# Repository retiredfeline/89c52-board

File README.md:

# 89c52 clock board

These are the design files for the 89C52 clock PCB described in [this Hackaday project](https://hackaday.io/project/175986-89c52-clock-board). It plugs onto the back of the [6 segment](https://hackaday.io/project/175397-6-segment-2-digit-led-display-board) and [7 segment](https://hackaday.io/project/175432-7-segment-2-digit-led-display-board) cascadable boards. The firmware is published at [89C52 clock](https://github.com/kenyapcomau/89c52-clock).

## Versioning

First release December 2020

## Notes

Not all the component locations on the board need to be populated, see the notes in the schematic.

## Authors

* **Ken Yap**

## License

See the [LICENSE](LICENSE.md) file for license rights and limitations (MIT).

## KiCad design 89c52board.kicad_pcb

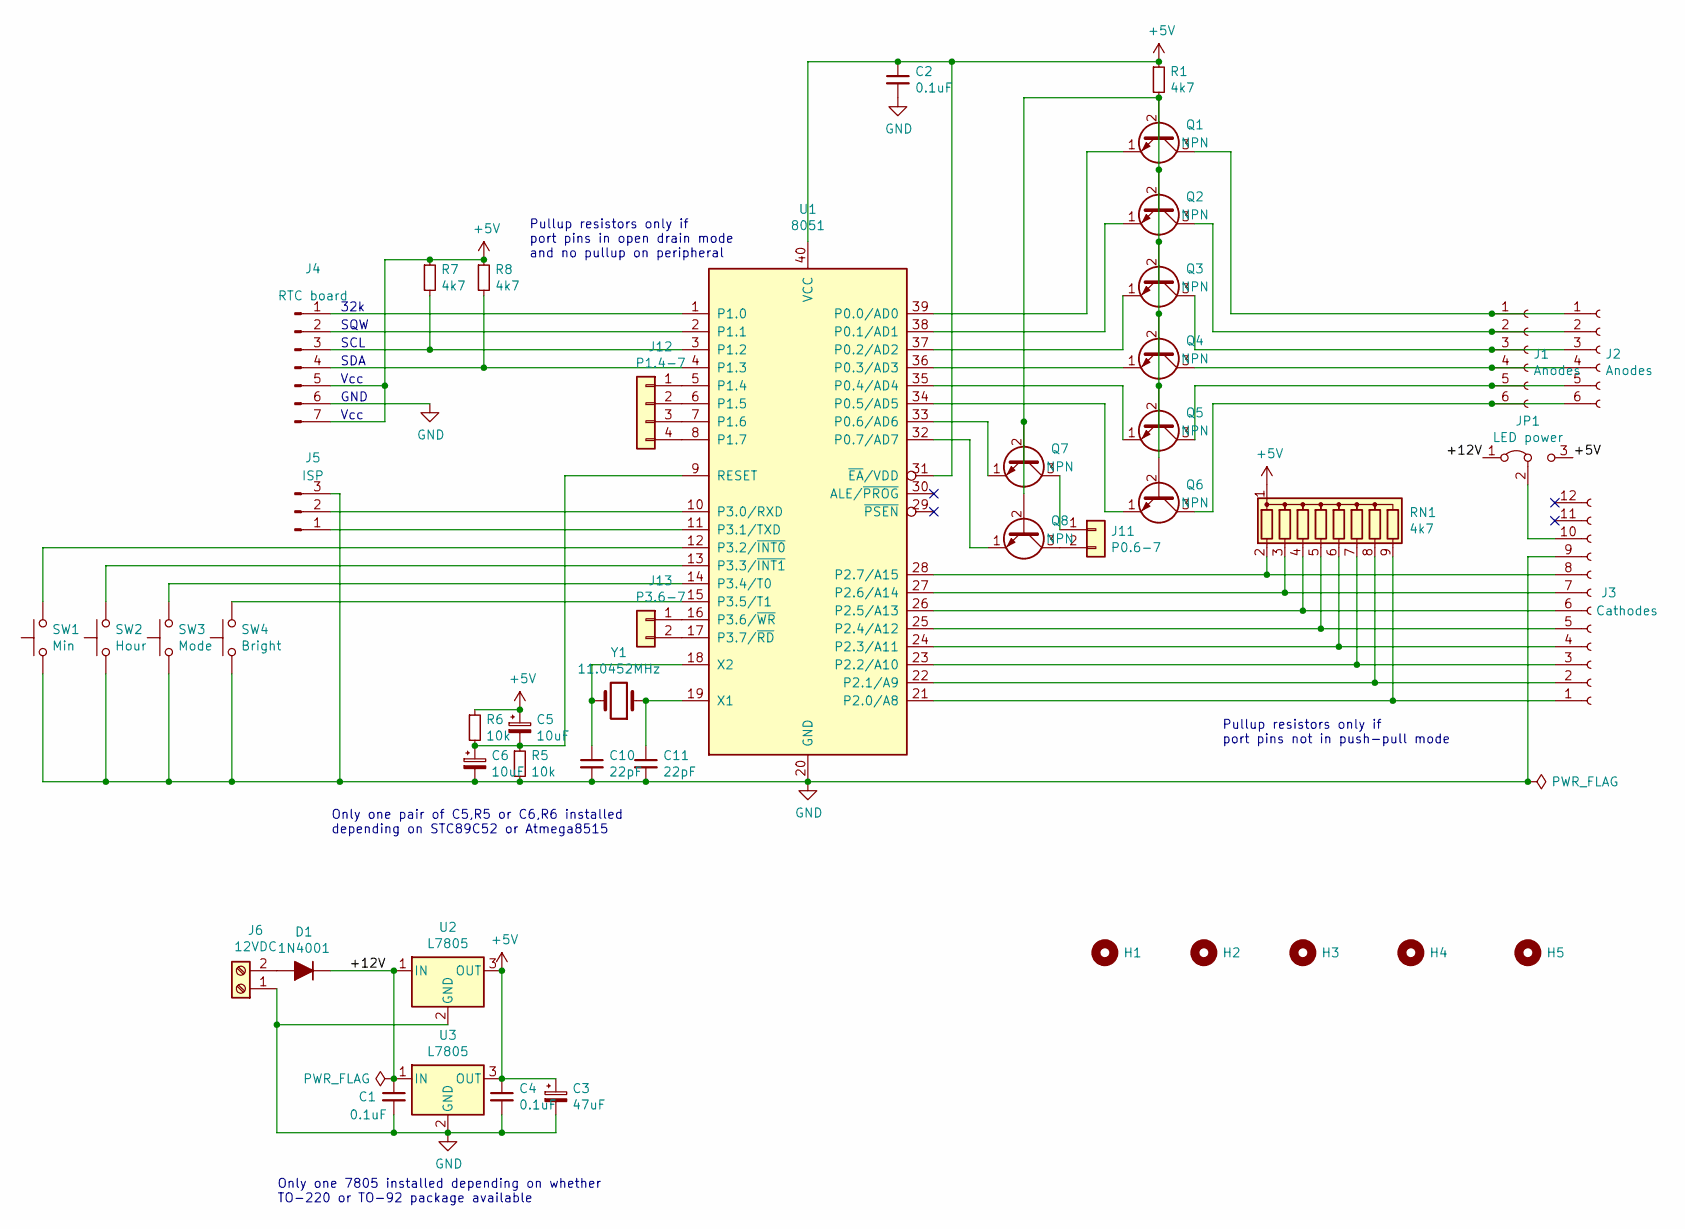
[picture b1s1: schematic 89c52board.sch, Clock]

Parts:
C1, C2, C4: 0.1uF; C_Disc_D3.8mm_W2.6mm_P2.50mm
C3: 47uF; CP_Radial_D5.0mm_P2.50mm
C5, C6: 10uF; CP_Radial_D5.0mm_P2.50mm
C10, C11: 22pF; C_Disc_D3.0mm_W1.6mm_P2.50mm
D1: 1N4001; D_DO-41_SOD81_P10.16mm_Horizontal
H1, H2, H3, H4: MountingHole; MountingHole_3.5mm
H5: MountingHole; MountingHole_4.5mm
J1, J2: Anodes; PinSocket_1x06_P2.54mm_Vertical
J3: Cathodes; PinSocket_1x12_P2.54mm_Vertical
J4: RTC board; PinHeader_1x07_P2.54mm_Vertical
J5: ISP; PinHeader_1x03_P2.54mm_Vertical
J6: 12VDC; TerminalBlock_bornier-2_P5.08mm
J11: P0.6-7; 1X02
J12: P1.4-7; 1X04
J13: P3.6-7; 1X02
JP1: LED power; PinHeader_1x03_P2.54mm_Vertical
Q1, Q2, Q3, Q4, Q5, Q6, Q7, Q8: NPN; TO-92
R1, R7, R8: 4k7; R_Axial_DIN0207_L6.3mm_D2.5mm_P10.16mm_Horizontal
R5, R6: 10k; R_Axial_DIN0207_L6.3mm_D2.5mm_P10.16mm_Horizontal
RN1: 4k7; R_Array_SIP9
SW1: Min; SW_PUSH_6mm_H5mm
SW2: Hour; SW_PUSH_6mm_H5mm
SW3: Mode; SW_PUSH_6mm_H5mm
SW4: Bright; SW_PUSH_6mm_H5mm
U1: 8051; DIP-40_W15.24mm
U2: L7805; TO-220-3_Vertical
U3: L7805; TO-92
Y1: 11.0452MHz; Crystal_HC49-4H_Vertical

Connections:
+5V: C2.1, C3.1, C4.1, C5.1, J4.5, J4.7, JP1.3 (B), R1.1, R6.1, R7.1, R8.1, RN1.1 (common), U1.31 (~EA~/VDD), U1.40 (VCC), U2.3 (OUT), U3.3 (OUT)
/+12V: C1.1, D1.1 (K), JP1.1 (A), U2.1 (IN), U3.1 (IN)
GND: C1.2, C2.2, C3.2, C4.2, C6.2, C10.2, C11.2, J3.9, J4.6, J5.3, J6.1, R5.2, SW1.1, SW2.1, SW3.1, SW4.1, U1.20 (GND), U2.2 (GND), U3.2 (GND)
unnamed: C5.2, C6.1, R5.1, R6.2, U1.9 (RESET)
unnamed: C10.1, U1.18 (X2), Y1.2
unnamed: C11.1, U1.19 (X1), Y1.1
unnamed: D1.2 (A), J6.2
unnamed: J1.1, J2.1, Q1.3 (C)
unnamed: J1.2, J2.2, Q2.3 (C)
unnamed: J1.3, J2.3, Q3.3 (C)
unnamed: J1.4, J2.4, Q4.3 (C)
unnamed: J1.5, J2.5, Q5.3 (C)
unnamed: J1.6, J2.6, Q6.3 (C)
unnamed: J3.1, RN1.9 (R8), U1.21 (P2.0/A8)
unnamed: J3.2, RN1.8 (R7), U1.22 (P2.1/A9)
unnamed: J3.3, RN1.7 (R6), U1.23 (P2.2/A10)
unnamed: J3.4, RN1.6 (R5), U1.24 (P2.3/A11)
unnamed: J3.5, RN1.5 (R4), U1.25 (P2.4/A12)
unnamed: J3.6, RN1.4 (R3), U1.26 (P2.5/A13)
unnamed: J3.7, RN1.3 (R2), U1.27 (P2.6/A14)
unnamed: J3.8, RN1.2 (R1), U1.28 (P2.7/A15)
unnamed: J3.10, JP1.2 (C)
unnamed: J4.1, U1.1 (P1.0)
unnamed: J4.2, U1.2 (P1.1)
unnamed: J4.3, R7.2, U1.3 (P1.2)
unnamed: J4.4, R8.2, U1.4 (P1.3)
unnamed: J5.1, U1.11 (P3.1/TXD)
unnamed: J5.2, U1.10 (P3.0/RXD)
unnamed: J11.1, Q7.3 (C)
unnamed: J11.2, Q8.3 (C)
unnamed: J12.1, U1.5 (P1.4)
unnamed: J12.2, U1.6 (P1.5)
unnamed: J12.3, U1.7 (P1.6)
unnamed: J12.4, U1.8 (P1.7)
unnamed: J13.1, U1.16 (P3.6/~WR~)
unnamed: J13.2, U1.17 (P3.7/~RD~)
unnamed: Q1.1 (E), U1.39 (P0.0/AD0)
unnamed: Q1.2 (B), Q2.2 (B), Q3.2 (B), Q4.2 (B), Q5.2 (B), Q6.2 (B), Q7.2 (B), Q8.2 (B), R1.2
unnamed: Q2.1 (E), U1.38 (P0.1/AD1)
unnamed: Q3.1 (E), U1.37 (P0.2/AD2)
unnamed: Q4.1 (E), U1.36 (P0.3/AD3)
unnamed: Q5.1 (E), U1.35 (P0.4/AD4)
unnamed: Q6.1 (E), U1.34 (P0.5/AD5)
unnamed: Q7.1 (E), U1.33 (P0.6/AD6)
unnamed: Q8.1 (E), U1.32 (P0.7/AD7)
unnamed: SW1.2, U1.12 (P3.2/~INT0~)
unnamed: SW2.2, U1.13 (P3.3/~INT1~)
unnamed: SW3.2, U1.14 (P3.4/T0)
unnamed: SW4.2, U1.15 (P3.5/T1)

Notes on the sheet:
Only one pair of C5,R5 or C6,R6 installed depending on STC89C52 or Atmega8515
Only one 7805 installed depending on whether TO-220 or TO-92 package available
SCL
SDA
Vcc
GND
32k
SQW
Pullup resistors only if port pins in open drain mode and no pullup on peripheral
Pullup resistors only if port pins not in push-pull mode

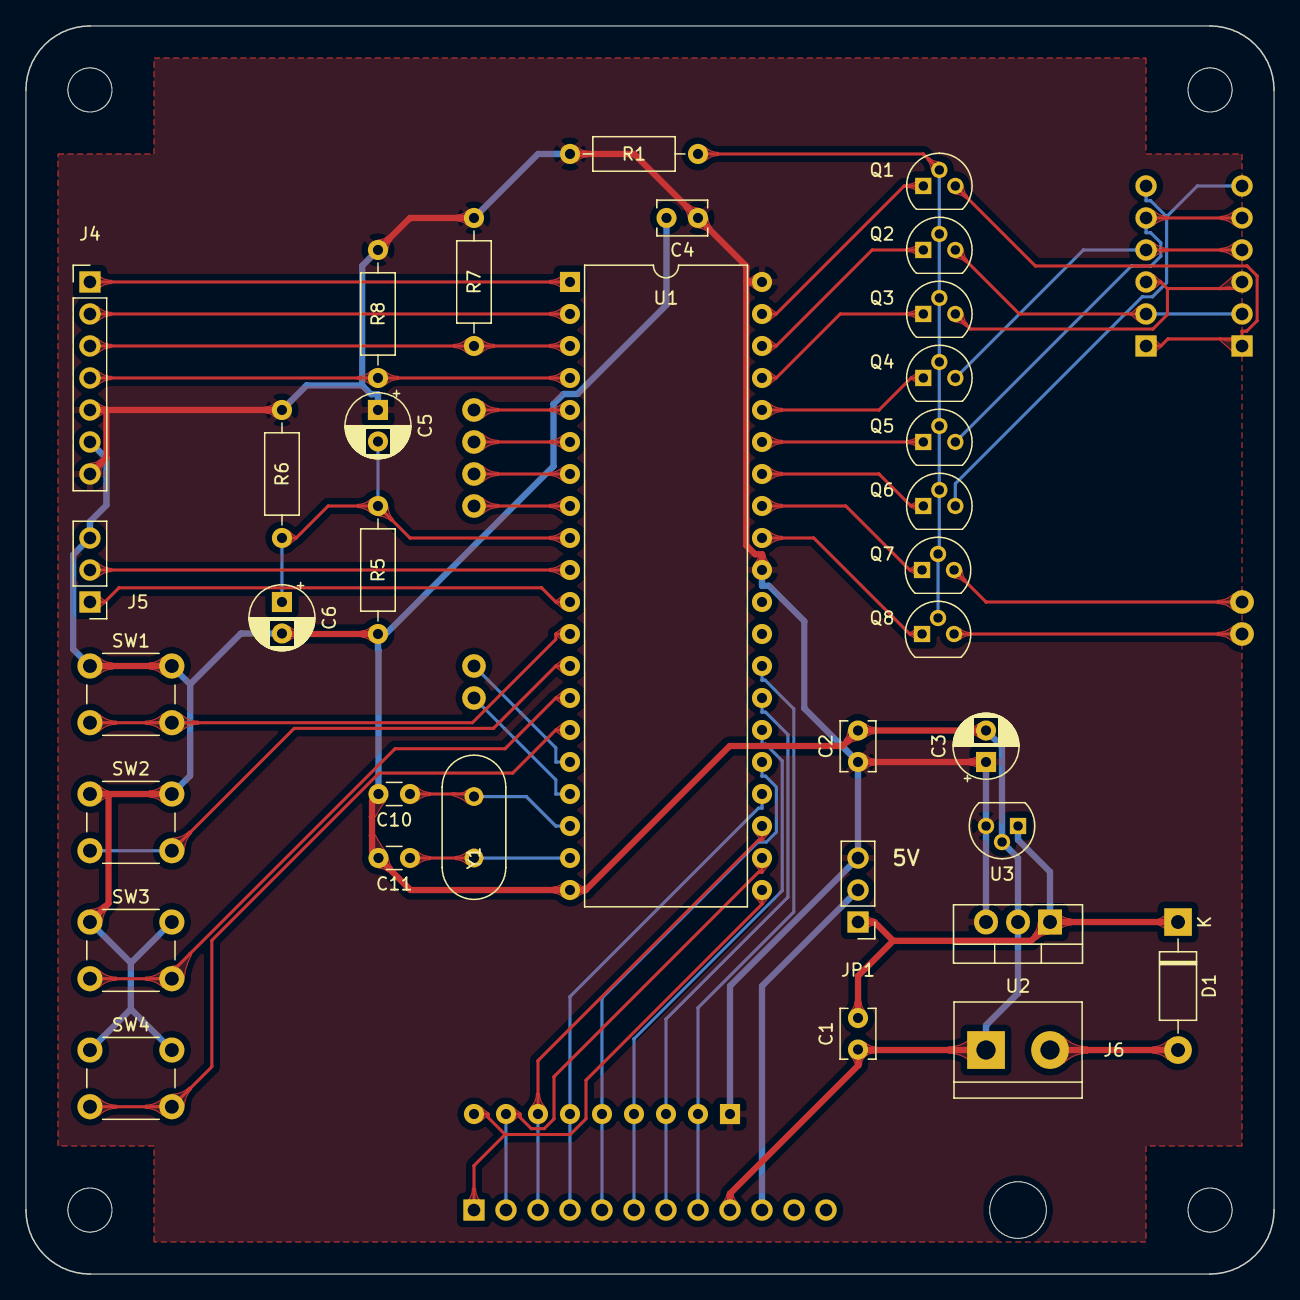
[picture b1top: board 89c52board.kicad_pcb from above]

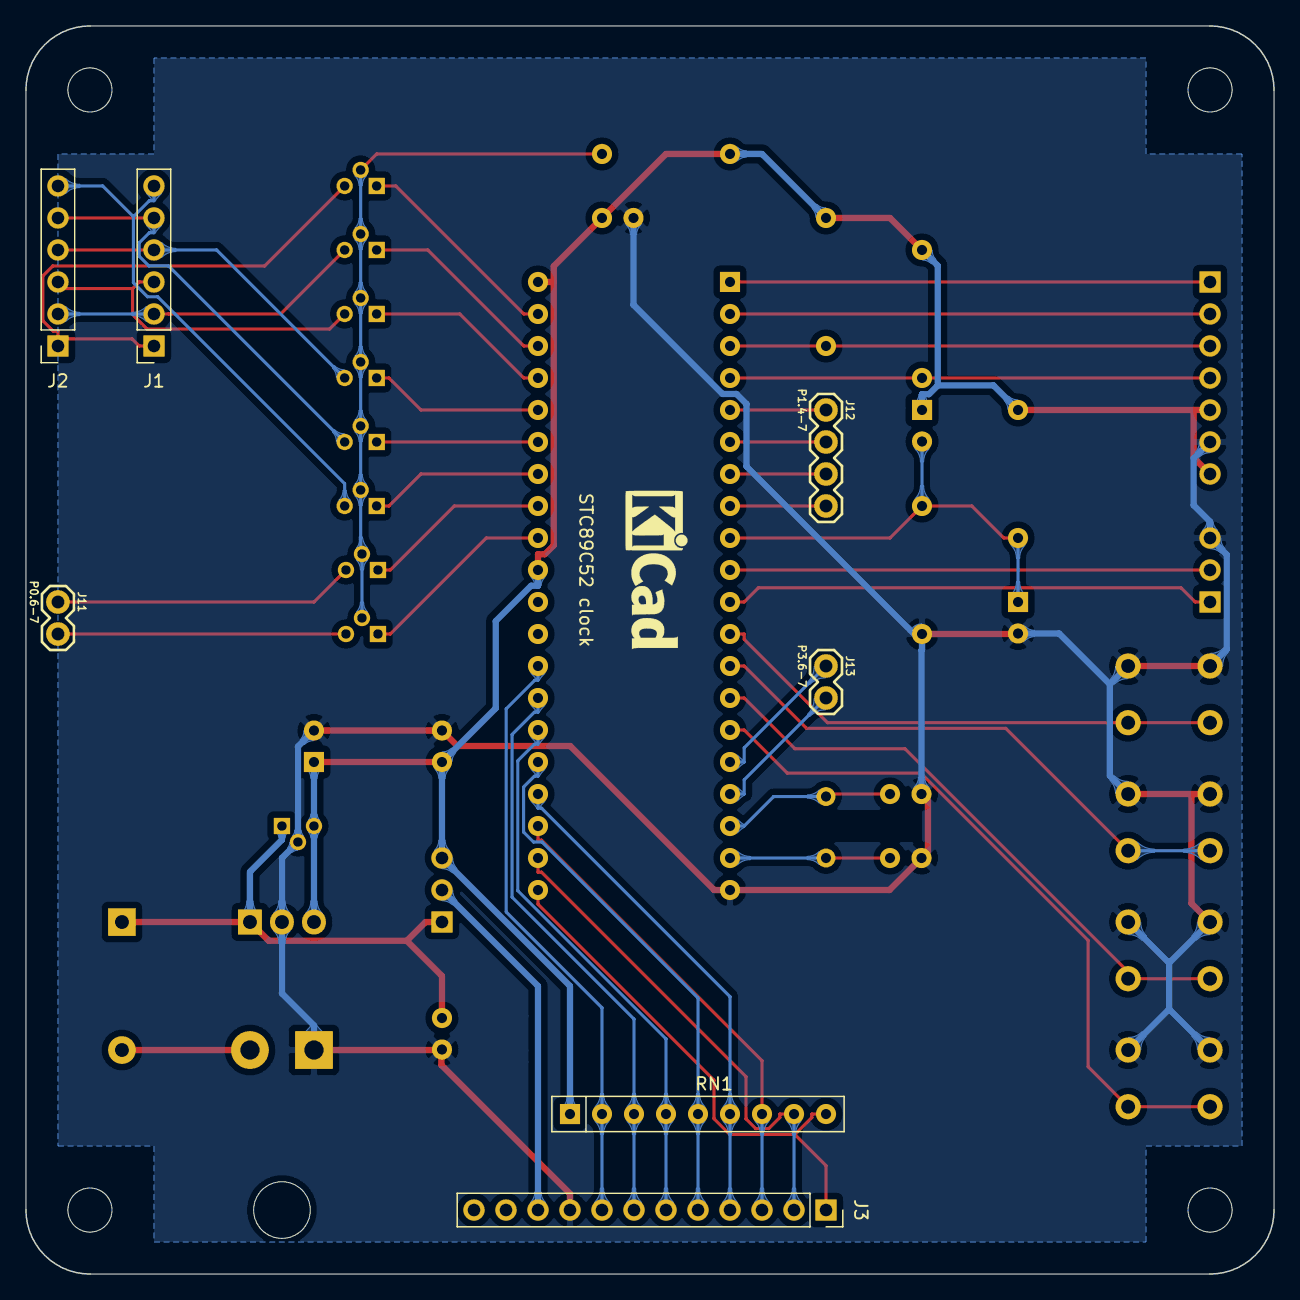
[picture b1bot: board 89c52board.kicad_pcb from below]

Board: 2 copper layers, 99.1 x 99.1 mm, 46 parts (7 on the bottom side), 49 nets.

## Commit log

2020-11-30 Cosmetic: swap C2 and C4 labels to better reflect their positions on board
2020-11-30 Cosmetic: update PDF also to avoid confusion
2021-08-31 More suitable values for I2C pullup resistors and digit driver transistor base resistor. Board unchanged
